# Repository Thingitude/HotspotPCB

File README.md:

# hotspotpcb
Hotspot PCB design
Design for a Pi 2 shield.  Contains RN2483 LoraWAN radio module, and a few sensors
Thanks to ThingInnovation for giving us a starting point, and Alex Gibson for helping with Eagle!

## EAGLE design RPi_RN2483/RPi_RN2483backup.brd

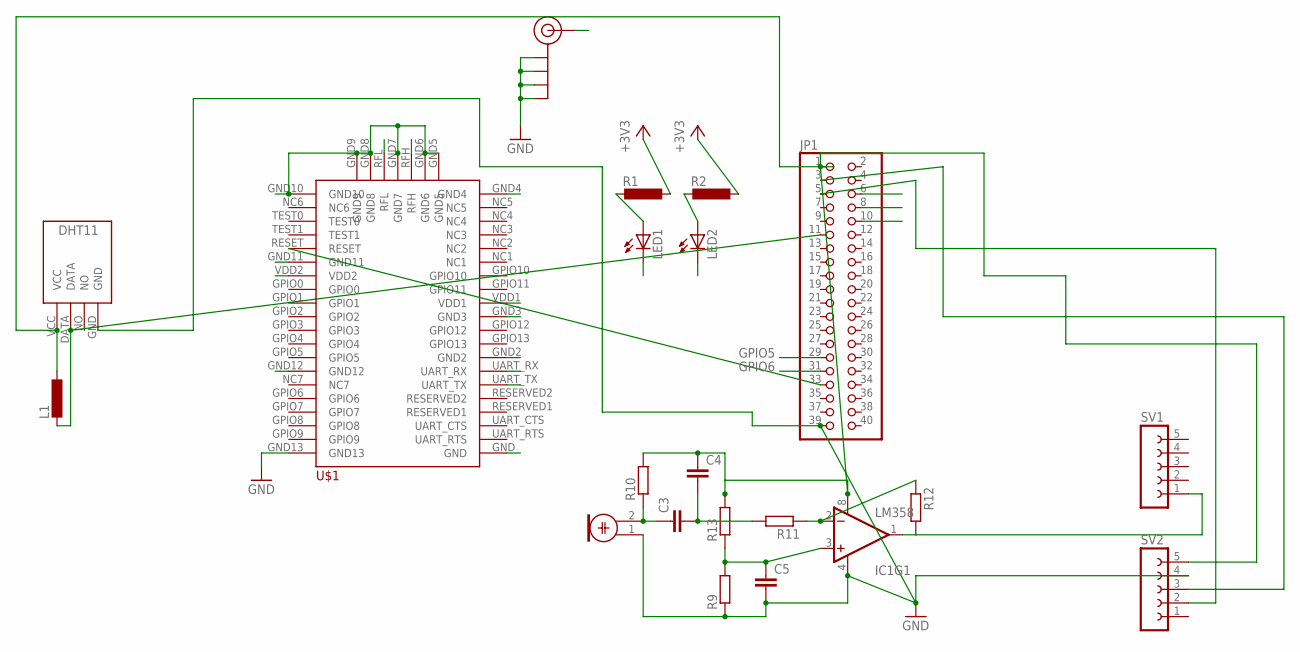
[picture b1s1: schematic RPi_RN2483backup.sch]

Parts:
C3, C4, C5: C-EU025-024X044; C025-024X044
IC1: LM358; DIP08
J$1: SMA_EDGE; SMA-EDGE
JP1: PINHD-2X20; 2X20
L1: L-EU0204/7; 0204/7
LED1, LED2: LED5MM
M1: ELECTRET_MICROPHON-F6050AP; F6050AP
R1, R2: L-EU0204/7; 0204/7
R9, R10, R11, R12, R13: R-EU_0204/7; 0204/7
SV1, SV2: FE05-1
U$1: RN2483
U$3: DHT11-PION.

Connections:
+3V3: C4.1, IC1.8 (V+), JP1.1, L1.1, R1.1, R2.1, R10.2, R13.2, SV2.5, U$1.VDD1, U$1.VDD2, U$3.VCC
GND: J$1.GND@0 (GND), J$1.GND@1 (GND), J$1.GND@2 (GND), J$1.GND@3 (GND), U$1.GND, U$1.GND2, U$1.GND3, U$1.GND4, U$1.GND5, U$1.GND6, U$1.GND7, U$1.GND8, U$1.GND9, U$1.GND10, U$1.GND11, U$1.GND12, U$1.GND13
GPIO5: JP1.29, LED1.K (C)
GPIO6: JP1.31, LED2.K (C)
GROUND: C5.2, IC1.4 (V-), JP1.6, JP1.39, M1.1, R9.1, SV2.4, U$3.GND
unnamed: LED1.A, R1.2
unnamed: LED2.A, R2.2
unnamed: JP1.11, L1.2, U$3.DATA
unnamed: IC1.2 (-IN), R11.1, R12.1
unnamed: JP1.33, U$1.RESET
unnamed: JP1.5, SV2.2
unnamed: JP1.3, SV2.3
unnamed: IC1.1 (OUT), R12.2, SV1.1
unnamed: C3.1, M1.2, R10.1
unnamed: C3.2, C4.2, R11.2
unnamed: C5.1, IC1.3 (+IN), R9.2, R13.1
RFH: J$1.SIG (SIGNAL), U$1.RFH
UART_RX: JP1.8, U$1.UART_RX
UART_TX: JP1.10, U$1.UART_TX

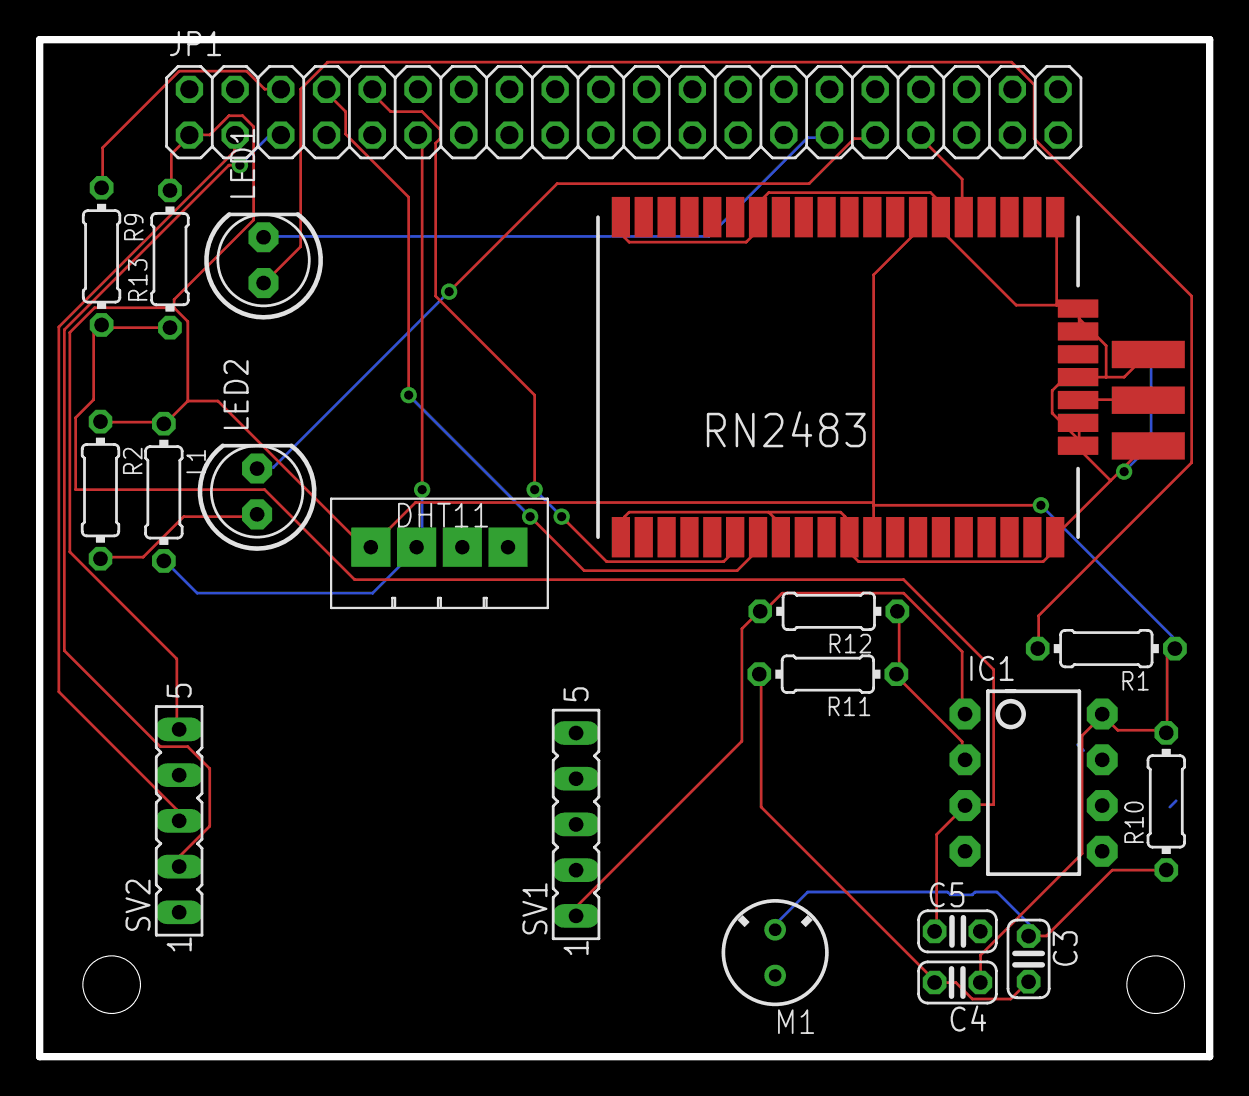
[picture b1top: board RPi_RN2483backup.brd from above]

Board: 2 copper layers, 65.0 x 56.5 mm, 21 parts (0 on the bottom side), 19 nets.

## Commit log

2016-07-28 First commit of Tom's design

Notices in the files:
parts and their libraries:
SparkFun-Connectors: Licensing: Creative Commons ShareAlike 4.0 International - https://creativecommons.org/licenses/by-sa/4.0
